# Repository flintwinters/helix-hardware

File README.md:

# Helix minimal hardware slice

KiCad 10 schematic for a USB powered STM32C071FBP6 with one shared SPI bus. The WIZ850io W5500 module and a **3.3 V, six wire microSD SPI breakout** have separate chip selects. SWD is available for first firmware bring-up.

Open `helix_minimal.kicad_pro` in KiCad. Run `python3 manage.py check` for label lint, ERC, and critical nets, or `python3 manage.py audit` for full DRC and every PCB pad net. The [PCB audit](docs/pcb_audit.md) records datasheet mappings and remaining risks. `python3 manage.py repair` fixes misplaced component reference/value fields in the existing schematic without rebuilding it. `python3 manage.py build` creates a schematic only when none exists. Building needs the KiCad 10 symbol library (`KICAD_SYMBOL_DIR` can point to it); the checked-in schematic and local symbols are self-contained.

## PCB routing

The PCB uses pinned [KiCadRoutingTools](https://github.com/drandyhaas/KiCadRoutingTools) (`git submodule update --init`). USB D+/D− were routed manually; the other signals were autorouted around them. Board Setup specifies 0.30 mm tracks and 0.20 mm clearance for ordinary nets. The USB connector class uses 0.15 mm tracks and clearance for USB D±, CC1/CC2, and VBUS; cross-class clearance is 0.20 mm. GND has F.Cu and B.Cu pours, with no GND tracks or vias. Both pours use thermal reliefs by default: in KiCad's [zone format](https://dev-docs.kicad.org/en/file-formats/sexpr-intro/index.html), omitting the `connect_pads` mode selects thermal reliefs, while `yes` selects solid connections. The four mounting-hole pads remain solid for mechanical grounding. Seven crowded GND pads use explicit solid connections because thermal reliefs there left only one spoke and failed DRC.

After manually connecting `/USB_DP` and `/USB_DM`, run `python3 manage.py route` on a preserved board. It removes other top-level tracks and vias from a working copy while retaining the manual USB copper, footprints, and both GND zones. It refuses to start until both USB data nets have copper, excludes them and GND from every autorouter net list, and verifies that their copper geometry survives the route. It routes CC1/CC2/VBUS first at 0.15 mm width, then SWCLK and the other ordinary nets at 0.30/0.20 mm. The USB pass omits `--clearance` so the router honors the 0.20 mm clearance against ordinary nets. It force-reroutes SPI MISO at 0.30 mm to remove the router's multipoint narrow taper, then force-reroutes +3V3 to remove a dangling via observed in the earlier 4000 turn-cost run. All passes use `--via-cost 300 --turn-cost 4000 --heuristic-weight 1.0 --same-net-pad-clearance 0.1 --grid-step 0.05 --via-size 0.4 --via-drill 0.2 --escalation off --strict-sizes --no-fix-drc-settings`. The router tries direction-preference costs 1200 and 2000 (F.Cu horizontal, B.Cu vertical), then installs the completed route with the smallest sum of squared non-USB net lengths plus an off-axis penalty. The original and intermediate boards remain in `.recovery/`. This is candidate selection; the pinned Rust A* search itself has no quadratic-length parameter. Run `python3 manage.py audit` after routing.

KiCad DRC reports no signal routing or thermal-relief violations and zero schematic parity issues. Two GND connections remain for manual review; 18 text-height warnings remain. The WIZ850io module body overlaps H3, R3, and R4 in a mechanical courtyard probe; resolve its assembly height and mechanical clearance before fabrication. J6 has SWCLK where an SPI accessory would need SCK.

The current route uses a 4000 turn cost and direction-preference cost 2000. All 24 manually drawn USB data copper items were preserved exactly. Its input and intermediate boards are recoverable in `.recovery/` if needed.

## Interfaces

| Interface | STM32 pads | Connector pins |
| --- | --- | --- |
| SPI1 SCK / MISO / MOSI | PA5 / PA6 / PA7 | WIZ850io U3.4 / U3.7 / U3.3; microSD J4.5 / J4.3 / J4.4 |
| W5500 select / interrupt / reset | PA4 / PA3 / PA0 | WIZ850io U3.5 / U3.6 / U3.8 |
| microSD select | PA8 | J4.6 |
| USB D− / D+ | PA11 / PA12 | J1 A7+B7 / A6+B6 |
| SWDIO / SWCLK / NRST | PA13 / PA14 / PF2 | J5.2 / J5.3 / J5.5 |

J4 is a **project-defined jumper header**, not a claimed footprint for a particular SD module: 1=GND, 2=3V3, 3=SO/MISO, 4=SI/MOSI, 5=CLK, 6=CS. Check the chosen breakout's physical pin order before wiring it. U3 combines WIZ850io J1 pins 1–6 with J2 pins 6–1 as footprint pads 1–12. Its board placement remains subject to DRC and mechanical review. Firmware should hold WIZ_RST low for at least 500 µs, then wait 50 ms after release before SPI access. Keep both CS lines high while neither device is selected.

The USB-C receptacle uses separate 5.1 kΩ CC pull-downs and a 3.3 V AP2112K regulator. C1 and C2 are the regulator's required 1 µF input/output capacitors; C3 is the MCU's 100 nF decoupling capacitor. VBUS, +3V3, and GND use KiCad power symbols connected by wires. There is no enclosure, firmware, USB ESD protection, or measured power budget. WIZ850io can draw about 141 mA by itself, so USB bus power behavior before configuration needs design review before claiming USB compliance.

## Source catalog

| Part | Local document | Verified design facts |
| --- | --- | --- |
| [STM32C071FBP6](https://www.st.com/resource/en/datasheet/stm32c071fb.pdf) | Official ST PDF linked; ST download endpoint timed out here | TSSOP20 pinout, SPI1 PA5/6/7, USB PA11/12, 2–3.6 V supply |
| [WIZ850io](https://docs.wiznet.io/Product/ioModule/WIZ850io) / [W5500](https://docs.wiznet.io/assets/files/W5500_ds_v110e-226ffec190c588b69f88d629789585e1.pdf) | `docs/wiz850io_schematic.pdf`, `docs/w5500.pdf` | 3.3 V module; two 1×6 headers; reset timing; about 141 mA normal operating current |
| [WIZ850io KiCad library](https://github.com/lorenzofattori/WIZ850io-KiCad-library) | `vendor/wiz850io/WIZ850io.lib`, `vendor/wiz850io/WIZ850io.kicad_sym`, `footprints/Helix.pretty/WIZ850io.kicad_mod` | Imported 12-pad symbol/footprint; 20.32 mm row spacing and 2.54 mm pitch match the module drawing. Socket pad drill enlarged from 0.762 to 1.0 mm to match the prior KiCad pin-socket footprints; module outline moved from silk to fabrication layer for clearance. Library is third-party; verify the actual module revision and mating socket before fabrication. |
| [AP2112K-3.3](https://www.diodes.com/datasheet/download/AP2112.pdf) | `docs/ap2112.pdf` | SOT-23-5, 600 mA rating, 1 µF input/output ceramic capacitors |
| [GCT USB4110](https://gct.co/files/specs/usb4110-spec.pdf) | `docs/usb4110.pdf` | USB 2.0 Type-C receptacle footprint and contact arrangement |
| [Adafruit 3 V microSD breakout guide](https://learn.adafruit.com/adafruit-microsd-spi-sdio/pinouts) | `docs/adafruit_microsd_breakout.pdf` | 3.3 V-only SPI signals; generic J4 follows signal names rather than its physical header order |

The local `Helix:AP2112K-3.3` symbol is the KiCad 10 library's inherited AP2112K symbol flattened for portability. The edited STM32 pin layout is stored in `symbols/STM32C071FBPx.kicad_sym`. The WIZ850io symbol was converted from the linked KiCad library with `kicad-cli sym upgrade`; its footprint was upgraded with `kicad-cli fp upgrade`. Other symbols come from the installed KiCad library.

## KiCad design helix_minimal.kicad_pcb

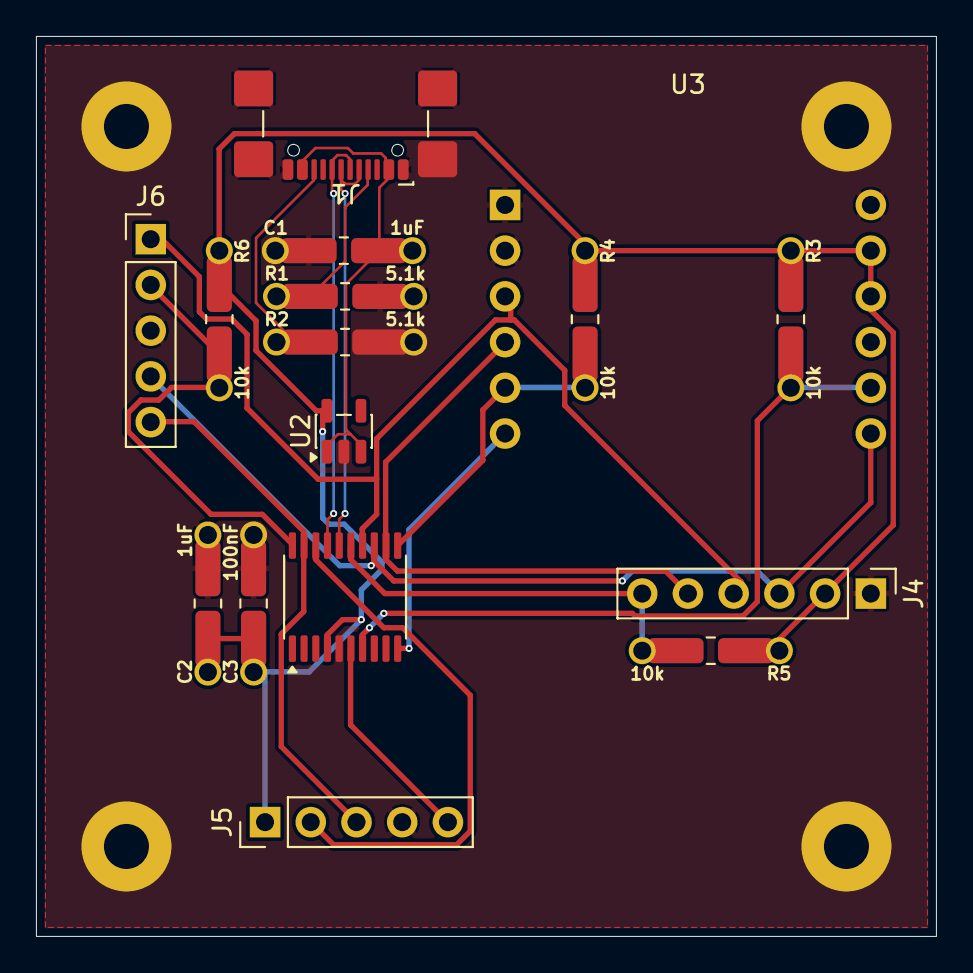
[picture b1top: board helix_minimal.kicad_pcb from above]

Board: 2 copper layers, 50.0 x 50.0 mm, 20 parts (0 on the bottom side), 18 nets.

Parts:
C1, C2: 1uF; R_0805_2012Metric_Pad1.20x1.40mm_HandSolder
C3: 100nF; R_0805_2012Metric_Pad1.20x1.40mm_HandSolder
H1, H2, H3, H4: MountingHole_Pad; MountingHole_2.5mm_Pad
J1: USB-C; USB_C_Receptacle_GCT_USB4110
J4: sd card; PinHeader_1x06_P2.54mm_Vertical
J5: SWD; PinHeader_1x05_P2.54mm_Vertical
J6: pico hdmi; PinHeader_1x05_P2.54mm_Vertical
R1, R2: 5.1k; R_0805_2012Metric_Pad1.20x1.40mm_HandSolder
R3, R4, R5, R6: 10k; R_0805_2012Metric_Pad1.20x1.40mm_HandSolder
U1: STM32C071FBP6; TSSOP-20_4.4x6.5mm_P0.65mm
U2: AP2112K-3.3; SOT-23-5
U3: WIZ850io

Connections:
+3V3: C2.1, C3.1, J4.2, J5.1, R3.1, R4.1, R5.1, R6.1, U1.4 (VDD), U2.5 (VOUT), U3.10 (3.3V), U3.11 (3.3V)
/CC1: J1.A5 (CC1), R1.1
/CC2: J1.B5 (CC2), R2.1
/NRST: J5.5, U1.6 (PF2)
/PICO_CS: J6.2, R6.2, U1.20 (PB3/PB4/PB5/PB6)
/SD_CS: J4.6, R5.2, U1.15 (PA8)
/SPI_MISO: J4.3, J6.4, U1.13 (PA6), U3.7 (MISO)
/SPI_MOSI: J4.4, J6.1, U1.14 (PA7), U3.3 (MOSI)
/SPI_SCK: J4.5, U1.12 (PA5), U3.4 (SCLK)
/SWCLK: J5.3, J6.5, U1.19 (PA14/PA15)
/SWDIO: J5.2, U1.18 (PA13)
/USB_DM: J1.A7 (D-), J1.B7 (D-), U1.16 (PA11)
/USB_DP: J1.A6 (D+), J1.B6 (D+), U1.17 (PA12)
/WIZ_CS: R4.2, U1.11 (PA4), U3.5 (SCNn)
/WIZ_INT: U1.10 (PA3), U3.6 (~INTn)
/WIZ_RST: R3.2, U1.7 (PA0), U3.8 (~RST)
GND: C1.1, C2.2, C3.2, H1.1 (1_1), H2.1 (1_1), H3.1 (1_1), H4.1 (1_1), J1.A1 (GND), J1.A12 (GND), J1.B1 (GND), J1.B12 (GND), J1.SH (SHIELD), J4.1, J5.4, J6.3, R1.2, R2.2, U1.5 (VSS), U2.2 (GND), U3.1 (GND), U3.2 (GND), U3.12 (GND)
VBUS: C1.2, J1.A4 (VBUS), J1.A9 (VBUS), J1.B4 (VBUS), J1.B9 (VBUS), U2.1 (VIN), U2.3 (EN)

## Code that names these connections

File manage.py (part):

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}

# STM32C071FBP6 TSSOP20 pad functions verified against ST DS14693, figure 4.
MCU_FUNCTIONS = {'4': 'VDD', '5': 'VSS', '6': 'PF2', '7': 'PA0',
                 '10': 'PA3', '11': 'PA4', '12': 'PA5', '13': 'PA6',
                 '14': 'PA7', '15': 'PA8', '16': 'PA11', '17': 'PA12',
                 '18': 'PA13', '19': 'PA14/PA15'}

FOOTPRINTS = {
    'J1': 'Connector_USB:USB_C_Receptacle_GCT_USB4110',
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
